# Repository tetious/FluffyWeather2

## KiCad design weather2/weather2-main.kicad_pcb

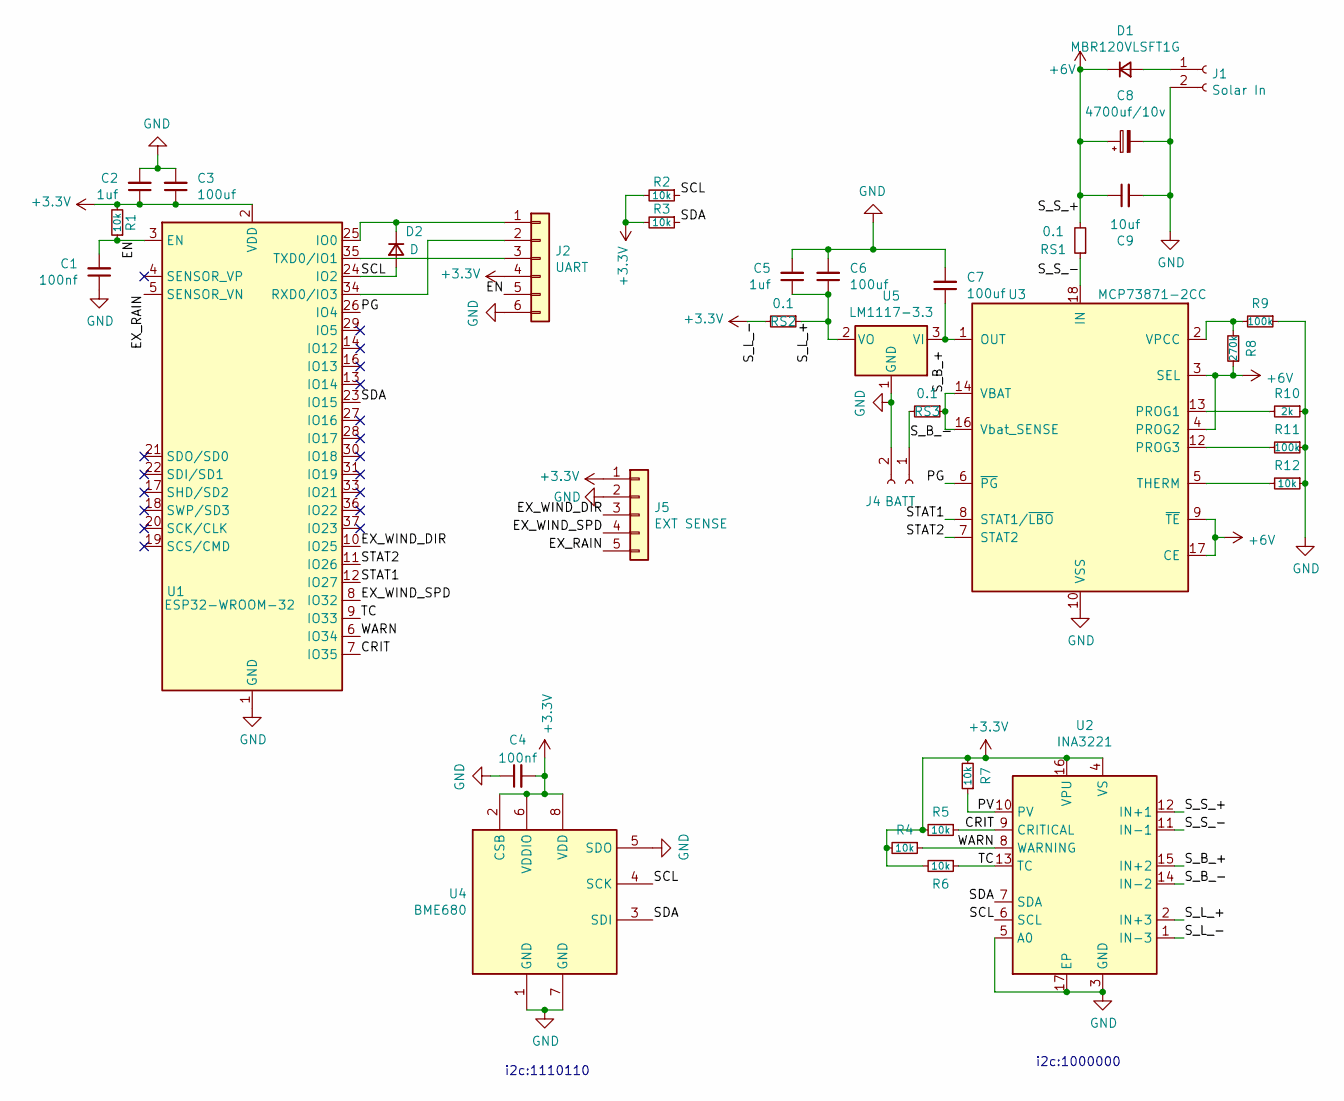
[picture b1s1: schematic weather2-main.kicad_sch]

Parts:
C1, C4: 100nf; C_0805_2012Metric_Pad1.15x1.40mm_HandSolder
C2, C5: 1uf; C_0805_2012Metric_Pad1.15x1.40mm_HandSolder
C3, C6, C7: 100uf; C_0805_2012Metric_Pad1.15x1.40mm_HandSolder
C8: 4700uf/10v; CP_Radial_D16.0mm_P7.50mm-SpaceSaver
C9: 10uf; C_0805_2012Metric_Pad1.15x1.40mm_HandSolder
D1: MBR120VLSFT1G; D_0805_2012Metric_Pad1.15x1.40mm_HandSolder
D2: D; D_0805_2012Metric_Pad1.15x1.40mm_HandSolder
J1: Solar In; PinHeader_1x02_P2.54mm_Vertical
J2: UART; PinHeader_1x06_P2.54mm_Vertical
J4: BATT; PinHeader_1x02_P2.54mm_Vertical
J5: EXT SENSE; PinHeader_1x05_P2.54mm_Vertical
R1, R2, R3, R4, R5, R6, R7, R12: 10k; R_0805_2012Metric_Pad1.15x1.40mm_HandSolder
R8: 270k; R_0805_2012Metric_Pad1.15x1.40mm_HandSolder
R9, R11: 100k; R_0805_2012Metric_Pad1.15x1.40mm_HandSolder
R10: 2k; R_0805_2012Metric_Pad1.15x1.40mm_HandSolder
RS1, RS2, RS3: 0.1; R_0805_2012Metric_Pad1.15x1.40mm_HandSolder
U1: ESP32-WROOM-32
U2: INA3221; Texas_RGV_S-PVQFN-N16_EP2.1x2.1mm
U3: MCP73871-2CC; QFN-20-1EP_4x4mm_P0.5mm_EP2.5x2.5mm
U4: BME680; Bosch_LGA-8_3x3mm_P0.8mm_ClockwisePinNumbering
U5: LM1117-3.3; TO-252-2

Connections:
+3V3: C2.1, C3.1, C4.2, J2.4, J5.1, R1.2, R2.2, R3.2, R4.2, R5.2, R6.2, R7.2, RS2.2, U1.2 (VDD), U2.1 (IN-3), U2.4 (VS), U2.16 (VPU), U4.2 (CSB), U4.6 (VDDIO), U4.8 (VDD)
+6V: C8.1, C9.1, D1.1 (K), R8.1, RS1.2, U2.12 (IN+1), U3.3 (SEL), U3.4 (PROG2), U3.9 (~TE), U3.17 (CE)
/CRIT: R5.1, U1.7 (IO35), U2.9 (CRITICAL)
/EN: C1.2, J2.5, R1.1, U1.3 (EN)
/EX_RAIN: J5.5, U1.5 (SENSOR_VN)
/EX_WIND_DIR: J5.3, U1.10 (IO25)
/EX_WIND_SPD: J5.4, U1.8 (IO32)
/PG: U1.26 (IO4), U3.6 (~PG)
/PV: R7.1, U2.10 (PV)
/SCL: D2.2 (A), R2.1, U1.24 (IO2), U2.6 (SCL), U4.4 (SCK)
/SDA: R3.1, U1.23 (IO15), U2.7 (SDA), U4.3 (SDI)
/STAT1: U1.12 (IO27), U3.8 (STAT1/~LBO)
/STAT2: U1.11 (IO26), U3.7 (STAT2)
/S_B_+: RS3.1, U2.15 (IN+2), U3.14 (VBAT), U3.15 (VBAT), U3.16 (Vbat_SENSE)
/S_B_-: J4.1, RS3.2, U2.14 (IN-2)
/S_L_+: C5.1, C6.1, RS2.1, U2.2 (IN+3), U5.2 (VO)
/S_S_-: RS1.1, U2.11 (IN-1), U3.18 (IN), U3.19 (IN)
/TC: R6.1, U1.9 (IO33), U2.13 (TC)
/WARN: R4.1, U1.6 (IO34), U2.8 (WARNING)
GND: C1.1, C2.2, C3.2, C4.1, C5.2, C6.2, C7.2, C8.2, C9.2, J1.2, J2.6, J4.2, J5.2, R9.1, R10.1, R11.1, R12.1, U1.1 (GND), U1.15 (GND), U1.38 (GND), U1.39 (GND), U2.3 (GND), U2.5 (A0), U2.17 (EP), U3.10 (VSS), U3.11 (VSS), U3.21 (VSS), U4.1 (GND), U4.5 (SDO), U4.7 (GND), U5.1 (GND)
unnamed: C7.1, U3.1 (OUT), U3.20 (OUT), U5.3 (VI)
unnamed: D1.2 (A), J1.1
unnamed: D2.1 (K), J2.1, U1.25 (IO0)
unnamed: J2.2, U1.34 (RXD0/IO3)
unnamed: J2.3, U1.35 (TXD0/IO1)
unnamed: R8.2, R9.2, U3.2 (VPCC)
unnamed: R10.2, U3.13 (PROG1)
unnamed: R11.2, U3.12 (PROG3)
unnamed: R12.2, U3.5 (THERM)

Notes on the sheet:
i2c:1110110
i2c:1000000

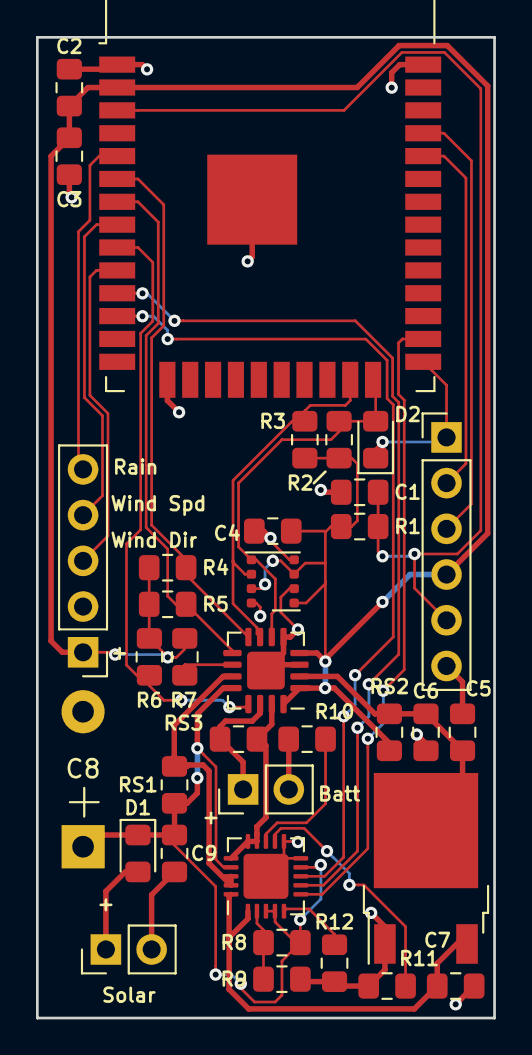
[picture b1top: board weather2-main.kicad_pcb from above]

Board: 2 copper layers, 25.4 x 54.5 mm, 35 parts (0 on the bottom side), 29 nets.

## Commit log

2020-04-30 Initial checkin.
2020-05-03 Complete schematic. Start of layout.
2020-05-03 1.0 board!
2020-05-16 Add starter docker-compose for server stack.
2020-05-16 Very WIP station code and half of repeater.
2020-05-17 Working repeater. Cleanups.
2020-05-17 More cleanups.
2020-05-18 Lots of stuff.
2023-07-04 Possibly final firmware.
2023-07-04 Add missing cache libs.
2023-07-04 Update to KiCad 7.
